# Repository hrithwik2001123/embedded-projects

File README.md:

# embedded-projects
A collection of embedded systems projects featuring microcontrollers, electronics, sensor interfacing, IoT, automation, firmware development, and hardware prototyping. Includes practical projects built using Arduino, ESP32, sensors, modules, and other embedded technologies.

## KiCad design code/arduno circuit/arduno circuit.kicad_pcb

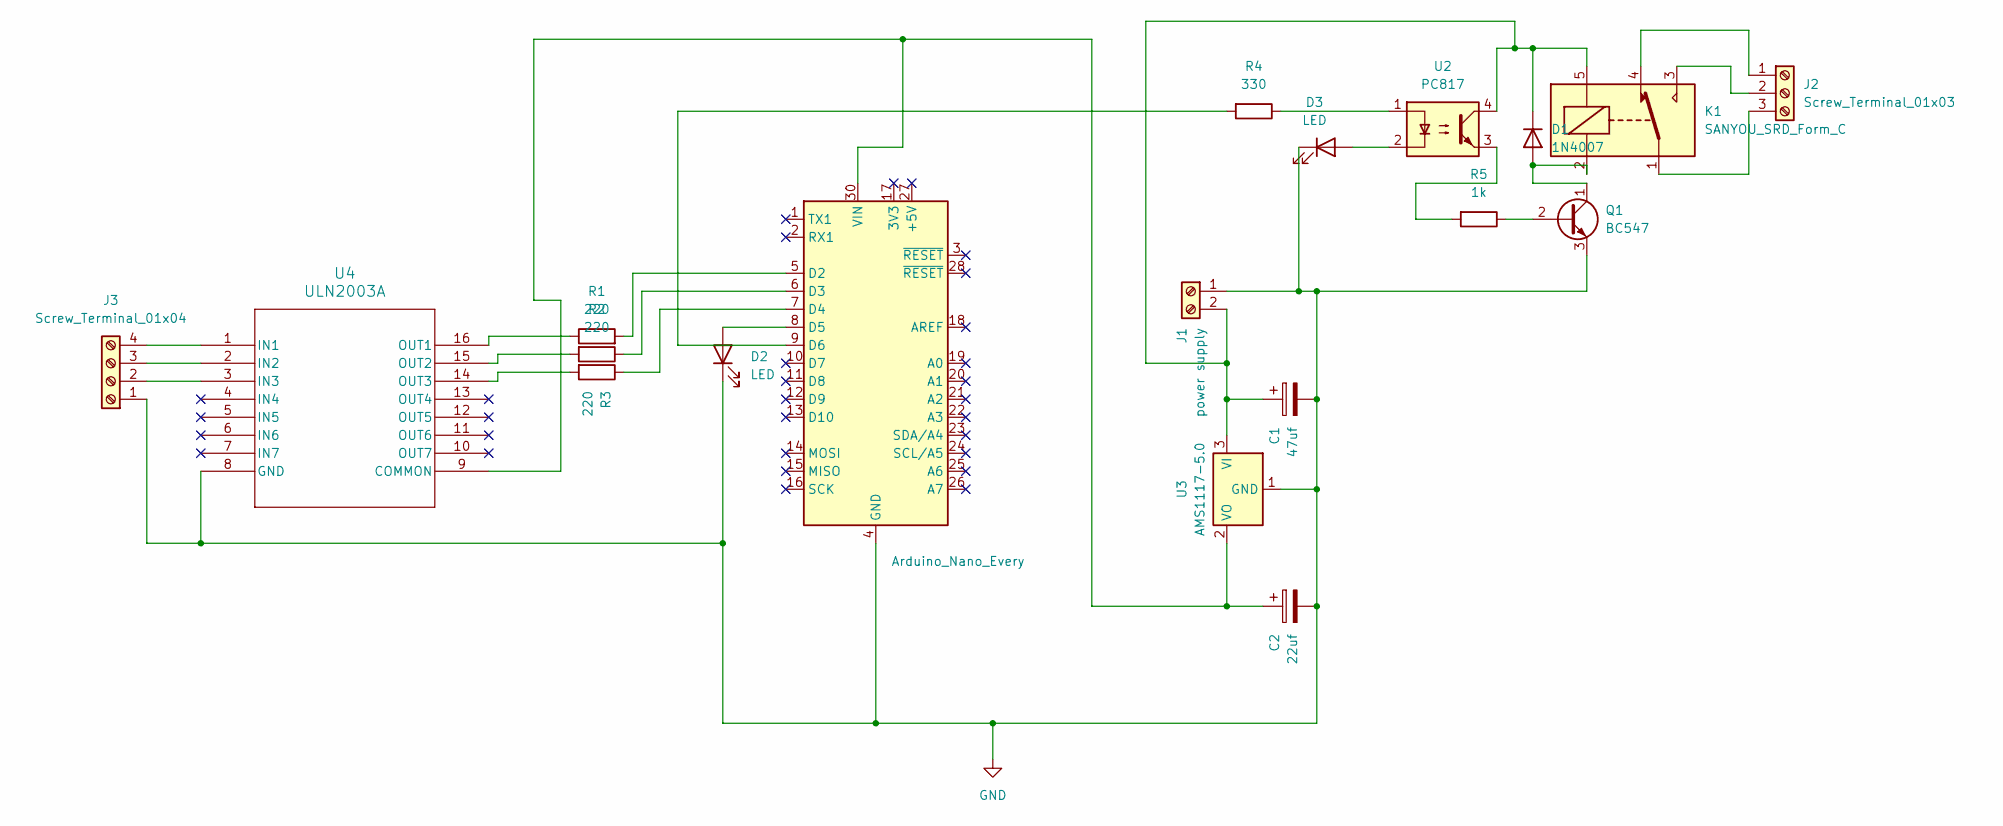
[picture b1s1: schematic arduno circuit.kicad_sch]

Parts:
A1: Arduino_Nano_Every; Arduino_Nano
C1: 47uf; C_Radial_D5.0mm_H11.0mm_P2.00mm
C2: 22uf; C_Radial_D6.3mm_H11.0mm_P2.50mm
D1: 1N4007; D_DO-41_SOD81_P10.16mm_Horizontal
D2, D3: LED; LED_D3.0mm_FlatTop
J1: power supply; TerminalBlock_MaiXu_MX126-5.0-02P_1x02_P5.00mm
J2: Screw_Terminal_01x03; TerminalBlock_MaiXu_MX126-5.0-03P_1x03_P5.00mm
J3: Screw_Terminal_01x04; TerminalBlock_MaiXu_MX126-5.0-04P_1x04_P5.00mm
K1: SANYOU_SRD_Form_C; Relay_SPDT_SANYOU_SRD_Series_Form_C
Q1: BC547; TO-92_Inline
R1, R2, R3: 220; R_Axial_DIN0204_L3.6mm_D1.6mm_P5.08mm_Horizontal
R4: 330; R_Axial_DIN0204_L3.6mm_D1.6mm_P5.08mm_Horizontal
R5: 1k; R_Axial_DIN0204_L3.6mm_D1.6mm_P5.08mm_Horizontal
U2: PC817; DIP-4_W7.62mm
U3: AMS1117-5.0; SOT-223-3_TabPin2
U4: ULN2003A

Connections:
GND: A1.4 (GND), A1.29 (GND), C1.2, C2.2, D2.1 (K), D3.1 (K), J1.1, J3.1, Q1.3 (E), U3.1 (GND), U4.8 (GND)
unnamed: A1.5 (D2), R1.2
unnamed: A1.6 (D3), R2.1
unnamed: A1.7 (D4), R3.1
unnamed: A1.8 (D5), D2.2 (A)
unnamed: A1.9 (D6), R4.2
unnamed: A1.30 (VIN), C2.1, U3.2 (VO), U4.9 (COMMON)
unnamed: D1.2 (A), K1.2, Q1.1 (C)
unnamed: C1.1, D1.1 (K), J1.2, K1.5, U2.4, U3.3 (VI)
unnamed: D3.2 (A), U2.2
unnamed: J2.1, K1.4
unnamed: J2.2, K1.3
unnamed: J2.3, K1.1
unnamed: J3.2, U4.3 (IN3)
unnamed: J3.3, U4.2 (IN2)
unnamed: J3.4, U4.1 (IN1)
unnamed: Q1.2 (B), R5.1
unnamed: R4.1, U2.1
unnamed: R5.2, U2.3
unnamed: R1.1, U4.16 (OUT1)
unnamed: R2.2, U4.15 (OUT2)
unnamed: R3.2, U4.14 (OUT3)

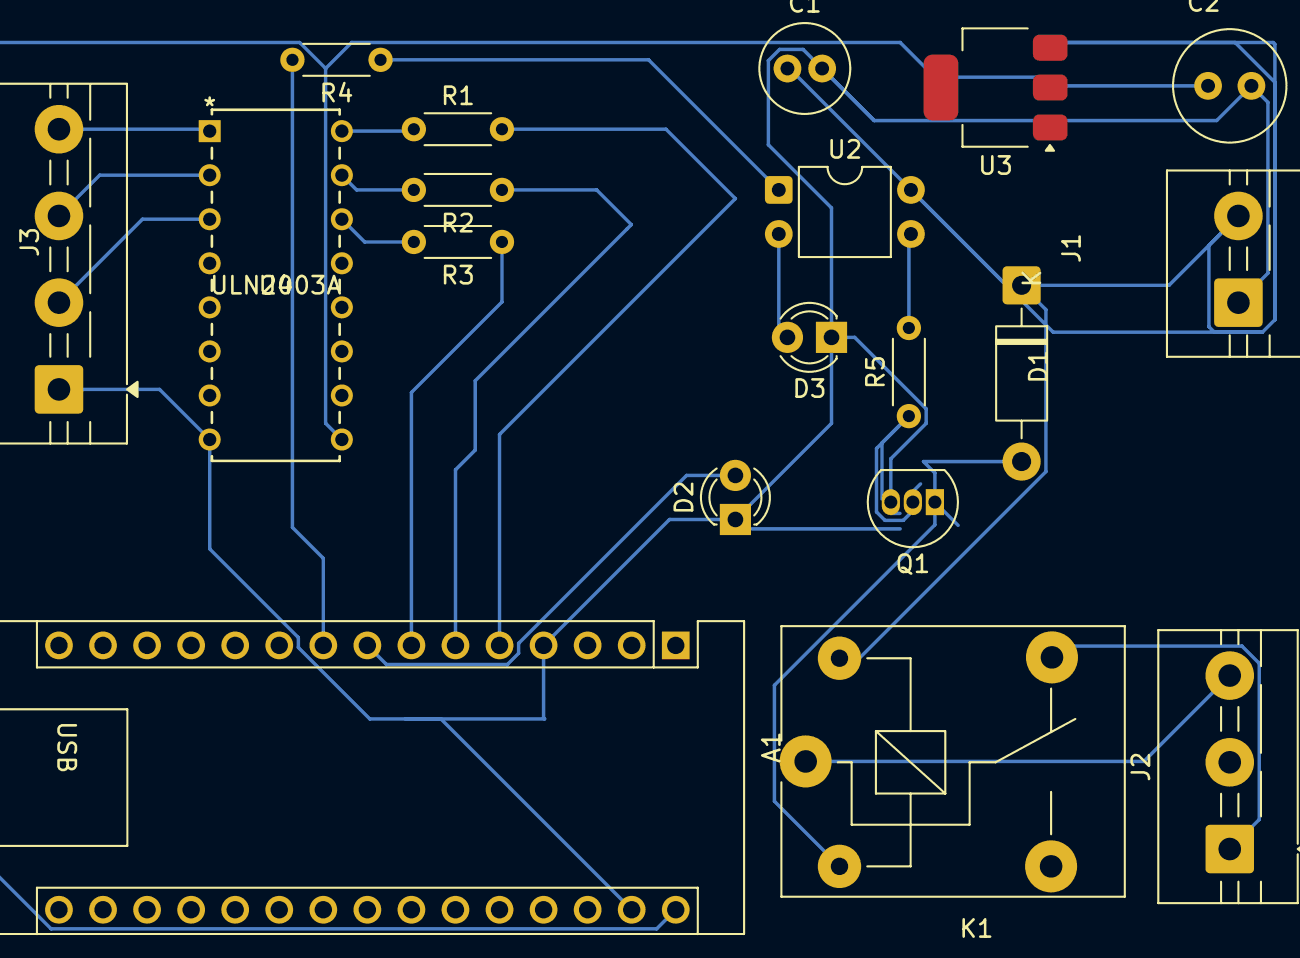
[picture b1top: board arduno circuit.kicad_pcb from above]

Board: 2 copper layers, 19 parts (0 on the bottom side), 22 nets.

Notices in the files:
parts and their libraries:
Copyright 2016 Accelerated Designs. All rights reserved.
